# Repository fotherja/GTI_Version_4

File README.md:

# GTI_Version_4
This repo contains the hardware and software files for GTIv4. This is being superseded by GTIv5 (https://github.com/fotherja/Grid_Tie_Inverter_V5)

Hardware:
KiCad was used to design the 4-Layer PCB. This was manufactured by <a href="https://www.pcbway.com/">PCBWay</a> (They produce good quality PCBs for competitive prices with excellent turnaround times).

The board uses gallium nitride MASTERGAN2s and an isolated driver chip. Four AMC1306 isolated current shunt modulators read the various analogue signals and an STM32L475 powers the board.    

Problems: 1) The EMC filter capacitors are incorrectly connected up. It may reduce the performance of the EMI filtering. 2) On testing, at about 300 Watts one of the MASTERGAN2s exploded. The exact reason is unclear and so this hardware has been redesigned into V5.

Software:
Software was developed in STM32CubeIDE. We got as far as implementing a PR controller which was extremely working well. Needs lots more work though.

Problems: I did not manage to get the DFSDM analogue watchdog feature working to provide protection in case of overcurrent or overvoltage. I asked the question on StackOverflow but got no answers (https://stackoverflow.com/questions/75287992/cant-get-the-analogue-watchdog-to-trigger-an-interrupt-on-the-dfsdm-peripheral)

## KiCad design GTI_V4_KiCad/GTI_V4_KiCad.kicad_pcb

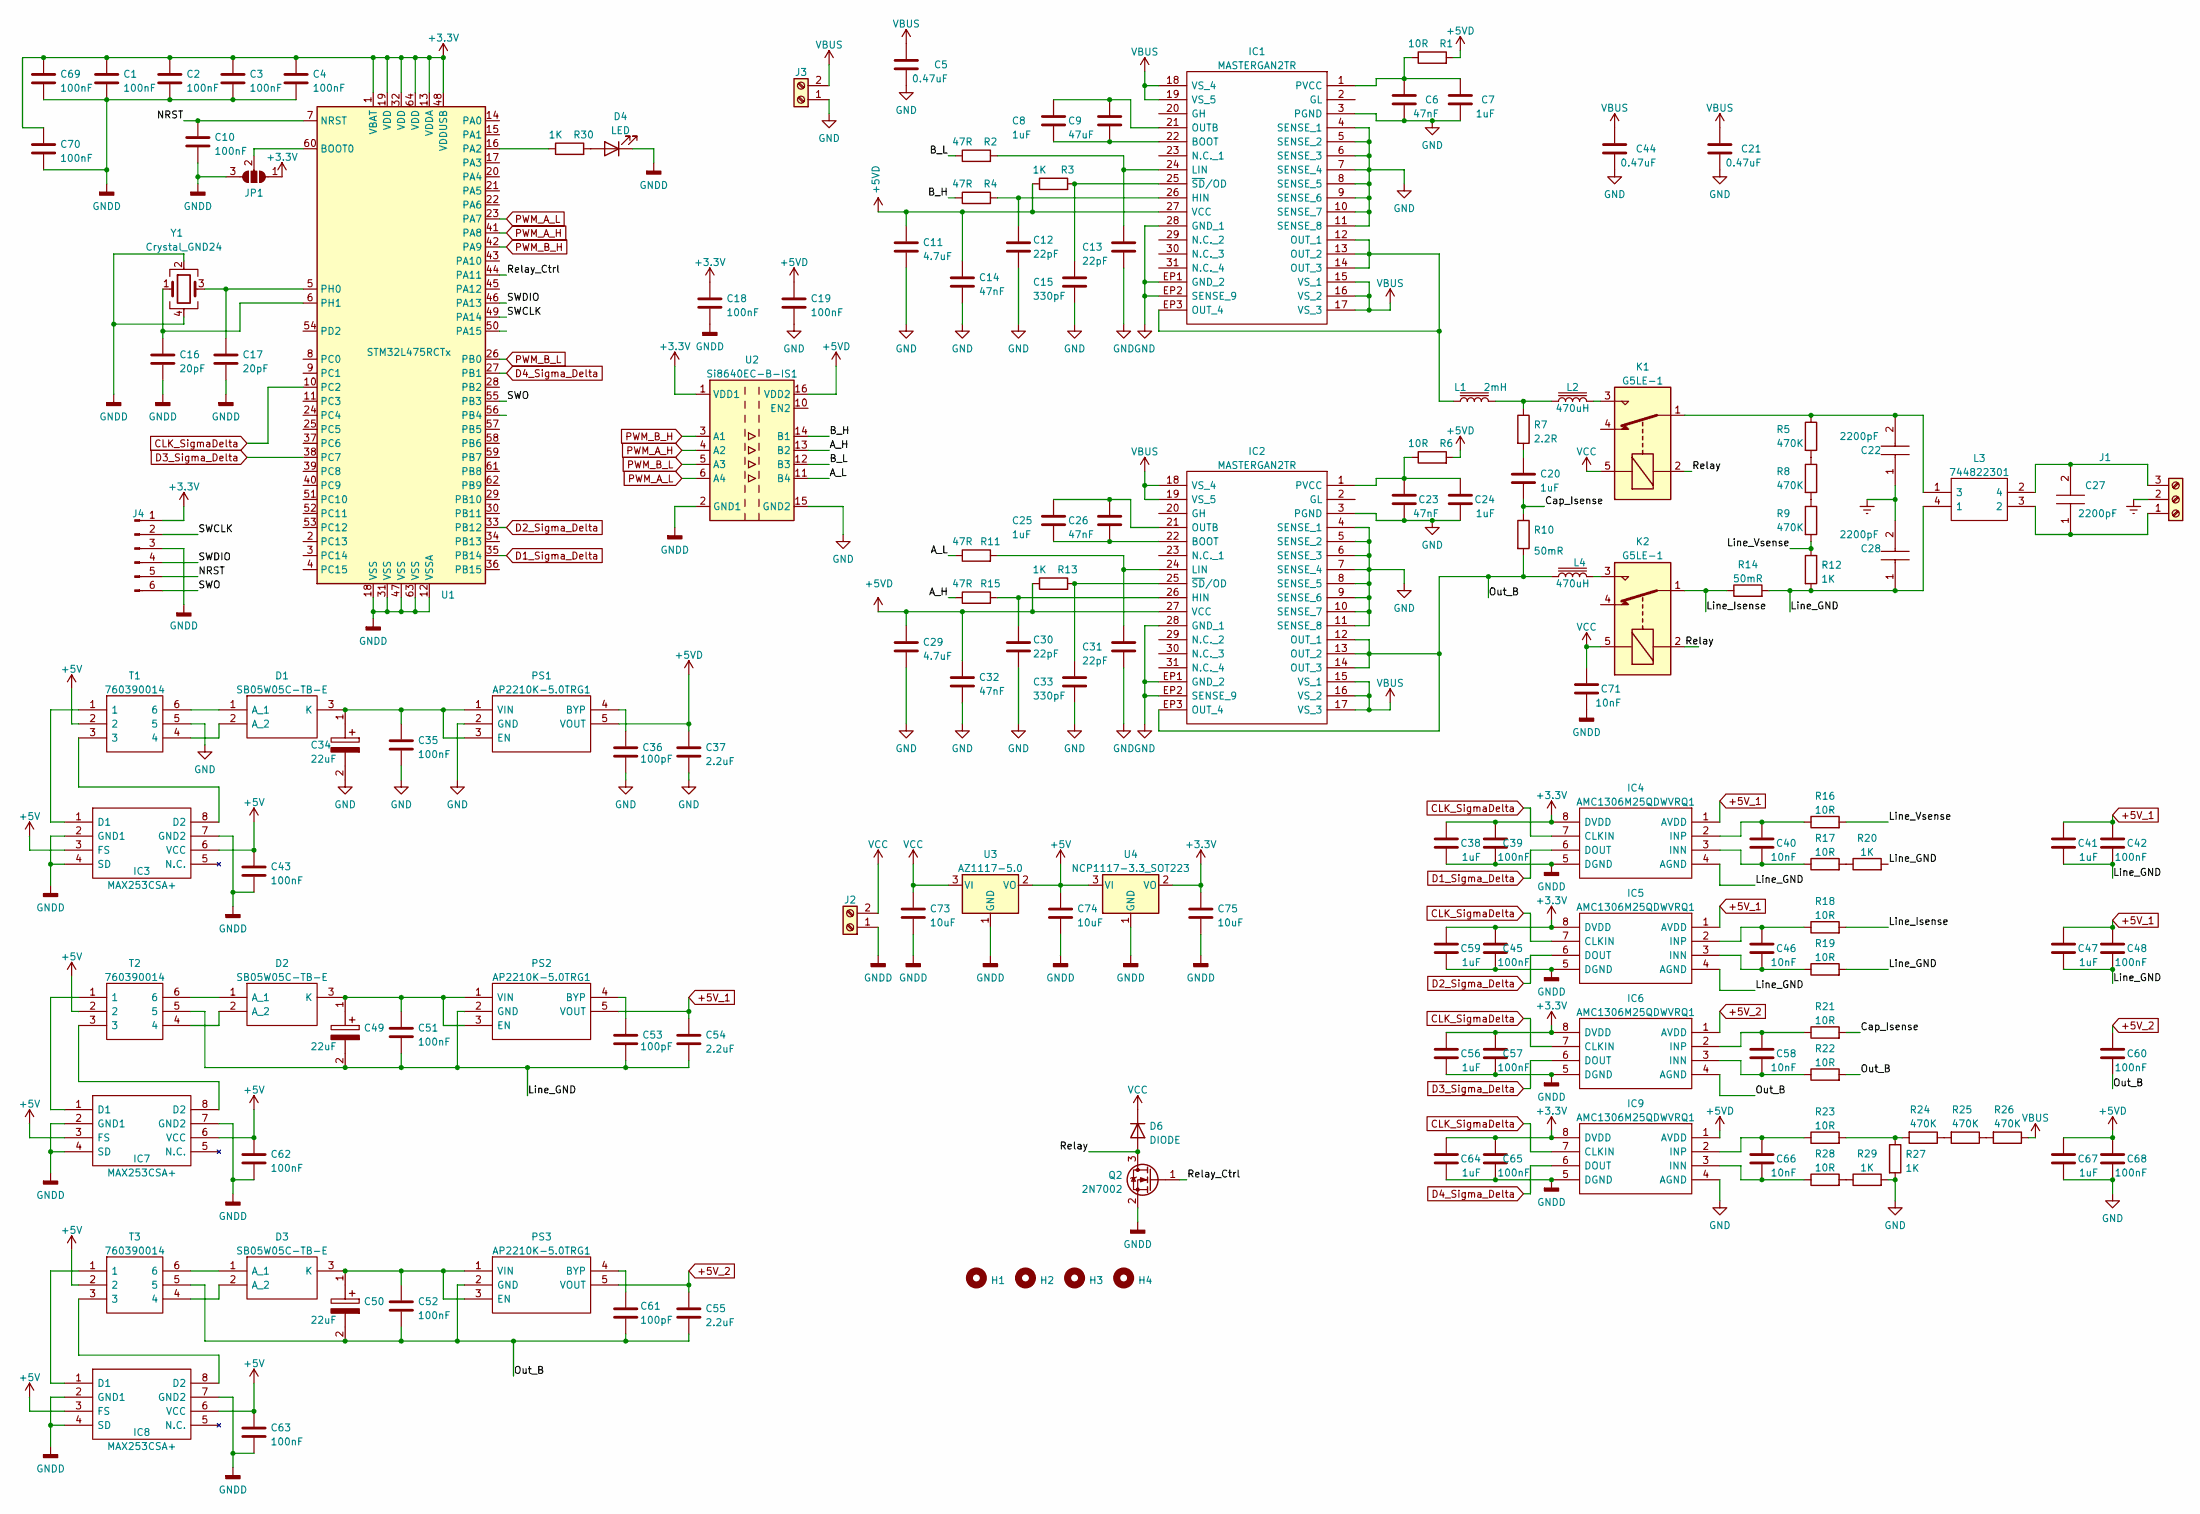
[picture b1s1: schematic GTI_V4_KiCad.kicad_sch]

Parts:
C1, C2, C3, C4, C10, C18, C19, C35, C39, C42, C43, C45, C48, C51, C52, C57, C60, C62, C63, C65, C68, C69, C70: 100nF; C_0603_1608Metric
C5, C21: 0.47uF; C_2225_5664Metric
C6, C14, C23, C26, C32: 47nF; C_0402_1005Metric
C7, C8, C24, C25, C38, C41, C47, C56, C59, C64, C67: 1uF; C_0603_1608Metric
C9: 47uF; C_0402_1005Metric
C11, C29: 4.7uF; C_0603_1608Metric
C12, C13, C30, C31: 22pF; C_0603_1608Metric
C15, C33: 330pF; C_0603_1608Metric
C16, C17: 20pF; C_0603_1608Metric
C20: 1uF; C_Rect_L27.0mm_W11.0mm_P22.00mm
C22, C27, C28: 2200pF; C901U222MZVDBA7317; Mouser Part Number 80-C901U222MZVDBAP
C34, C49, C50: 22uF; CAPPC3328X220N; Mouser Part Number 74-595D226X9020B2T
C36, C53, C61: 100pF; C_0603_1608Metric
C37, C54, C55: 2.2uF; C_0603_1608Metric
C40, C46, C58, C66, C71: 10nF; C_0603_1608Metric
C44: 0.47uF; C_Rect_L31.5mm_W17.0mm_P27.50mm_MKS4
C73: 10uF; C_0805_2012Metric
C74, C75: 10uF; C_0603_1608Metric
D1, D2, D3: SB05W05C-TB-E; SOT95P250X135-3N; Mouser Part Number 863-SB05W05C-TB-E
D4: LED; LED_0603_1608Metric
D6: DIODE; DIOM5227X250N
H1, H2, H3, H4: MountingHole; MountingHole_3.2mm_M3
IC1, IC2: MASTERGAN2TR; Mouser Part Number 511-MASTERGAN2TR
IC3, IC7, IC8: MAX253CSA+; SOIC127P600X175-8N; Mouser Part Number 700-MAX253CSA
IC4, IC5, IC6, IC9: AMC1306M25QDWVRQ1; SOIC127P1150X280-8N; Mouser Part Number 595-MC1306M25QDWVRQ1
J1: Screw_Terminal_01x03; TerminalBlock_bornier-3_P5.08mm
J2, J3: Screw_Terminal_01x02; TerminalBlock_bornier-2_P5.08mm
J4: Conn_01x06_Male; PinHeader_1x06_P1.27mm_Vertical
JP1: SolderJumper_3_Open; SolderJumper-3_P1.3mm_Open_RoundedPad1.0x1.5mm
K1, K2: G5LE-1; Relay_SPDT_Omron-G5LE-1
L1: 2mH; L_Toroid_Vertical_L35.1mm_W21.1mm_P18.50mm_Vishay_TJ6
L2, L4: 470uH; L_Toroid_Vertical_L41.9mm_W19.1mm_P15.80mm_Vishay_TJ7
L3: 744822301; WE-CMB_S5; Mouser Part Number 710-744822301
PS1, PS2, PS3: AP2210K-5.0TRG1; SOT95P282X130-5N; Mouser Part Number 621-AP2210K-5.0TRG1
Q2: 2N7002; SOT-23
R1, R6, R16, R17, R18, R19, R21, R22, R23, R28: 10R; R_0603_1608Metric
R2, R4, R11, R15: 47R; R_0603_1608Metric
R3, R12, R13, R20, R27, R29, R30: 1K; R_0603_1608Metric
R5, R8, R9, R24, R25, R26: 470K; R_0805_2012Metric
R7: 2.2R; R_2512_6332Metric
R10, R14: 50mR; R_2512_6332Metric
T1, T2, T3: 760390014; 760390015; Mouser Part Number 710-760390014
U1: STM32L475RCTx; LQFP-64_10x10mm_P0.5mm
U2: Si8640EC-B-IS1; SOIC-16_3.9x9.9mm_P1.27mm
U3: AZ1117-5.0; AZ1117CD50TRG1
U4: NCP1117-3.3_SOT223; SOT-223-3_TabPin2
Y1: Crystal_GND24; Crystal_SMD_Abracon_ABM10-4Pin_2.5x2.0mm

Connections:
+3.3V: C1.1, C2.1, C3.1, C4.1, C18.1, C38.1, C39.1, C45.1, C56.1, C57.1, C59.1, C64.1, C65.1, C69.1, C70.1, C75.1, IC4.8 (DVDD), IC5.8 (DVDD), IC6.8 (DVDD), IC9.8 (DVDD), J4.1, JP1.1 (A), U1.1 (VBAT), U1.13 (VDDA), U1.19 (VDD), U1.32 (VDD), U1.48 (VDDUSB), U1.64 (VDD), U2.1 (VDD1), U4.2 (VO)
+5V: C43.1, C62.1, C63.1, C74.1, IC3.3 (FS), IC3.6 (VCC), IC7.3 (FS), IC7.6 (VCC), IC8.3 (FS), IC8.6 (VCC), T1.2, T2.2, T3.2, U3.2 (VO), U4.3 (VI)
+5VD: C11.1, C14.1, C19.1, C29.1, C32.1, C37.1, C67.1, C68.1, IC1.27 (VCC), IC2.27 (VCC), IC9.1 (AVDD), PS1.5 (VOUT), R1.2, R3.1, R6.2, R13.1, U2.16 (VDD2)
+5V_1: C41.1, C42.1, C47.1, C48.1, C54.1, IC4.1 (AVDD), IC5.1 (AVDD), PS2.5 (VOUT)
+5V_2: C55.1, C60.1, IC6.1 (AVDD), PS3.5 (VOUT)
/A_H: R15.1, U2.13 (B2)
/A_L: R11.1, U2.11 (B4)
/B_H: R4.1, U2.14 (B1)
/B_L: R2.1, U2.12 (B3)
/Cap_Isense: C20.2, R10.1, R21.2
/Line_GND: C28.1, C41.2, C42.2, C47.2, C48.2, C49.2, C51.2, C53.2, C54.2, IC4.4 (AGND), IC5.4 (AGND), L3.4 (1), PS2.2 (GND), R12.2, R14.2, R19.2, R20.2, T2.5
/Line_Isense: K2.1, R14.1, R18.2
/Line_Vsense: R9.2, R12.1, R16.2
/NRST: C10.1, J4.5, U1.7 (NRST)
/Out_B: C50.2, C52.2, C55.2, C60.2, C61.2, IC2.12 (OUT_1), IC2.13 (OUT_2), IC2.14 (OUT_3), IC2.EP3 (OUT_4), IC6.4 (AGND), L4.1, PS3.2 (GND), R10.2, R22.2, T3.5
/Relay: D6.1 (A), K1.2, K2.2, Q2.3 (D)
/Relay_Ctrl: Q2.1 (G), U1.44 (PA11)
/SWCLK: J4.2, U1.49 (PA14)
/SWDIO: J4.4, U1.46 (PA13)
/SWO: J4.6, U1.55 (PB3)
CLK_SigmaDelta: IC4.7 (CLKIN), IC5.7 (CLKIN), IC6.7 (CLKIN), IC9.7 (CLKIN), U1.10 (PC2)
D1_Sigma_Delta: IC4.6 (DOUT), U1.35 (PB14)
D2_Sigma_Delta: IC5.6 (DOUT), U1.33 (PB12)
D3_Sigma_Delta: IC6.6 (DOUT), U1.38 (PC7)
D4_Sigma_Delta: IC9.6 (DOUT), U1.27 (PB1)
Earth: C22.1, C28.2, J1.2
GND: C5.2, C6.2, C7.2, C11.2, C12.2, C13.2, C14.2, C15.2, C19.2, C21.2, C23.2, C24.2, C29.2, C30.2, C31.2, C32.2, C33.2, C34.2, C35.2, C36.2, C37.2, C44.2, C67.2, C68.2, IC1.3 (PGND), IC1.4 (SENSE_1), IC1.5 (SENSE_2), IC1.6 (SENSE_3), IC1.7 (SENSE_4), IC1.8 (SENSE_5), IC1.9 (SENSE_6), IC1.10 (SENSE_7), IC1.11 (SENSE_8), IC1.28 (GND_1), IC1.EP1 (GND_2), IC1.EP2 (SENSE_9), IC2.3 (PGND), IC2.4 (SENSE_1), IC2.5 (SENSE_2), IC2.6 (SENSE_3), IC2.7 (SENSE_4), IC2.8 (SENSE_5), IC2.9 (SENSE_6), IC2.10 (SENSE_7), IC2.11 (SENSE_8), IC2.28 (GND_1), IC2.EP1 (GND_2), IC2.EP2 (SENSE_9), IC9.4 (AGND), J3.1, PS1.2 (GND), R27.2, R29.2, T1.5, U2.9 (GND2), U2.15 (GND2)
GNDD: C1.2, C2.2, C3.2, C4.2, C10.2, C16.2, C17.2, C18.2, C38.2, C39.2, C43.2, C45.2, C56.2, C57.2, C59.2, C62.2, C63.2, C64.2, C65.2, C69.2, C70.2, C71.2, C73.2, C74.2, C75.2, D4.1 (K), IC3.2 (GND1), IC3.4 (SD), IC3.7 (GND2), IC4.5 (DGND), IC5.5 (DGND), IC6.5 (DGND), IC7.2 (GND1), IC7.4 (SD), IC7.7 (GND2), IC8.2 (GND1), IC8.4 (SD), IC8.7 (GND2), IC9.5 (DGND), J2.1, J4.3, JP1.3 (B), Q2.2 (S), U1.12 (VSSA), U1.18 (VSS), U1.31 (VSS), U1.47 (VSS), U1.63 (VSS), U2.2 (GND1), U2.8 (GND1), U3.1 (GND), U4.1 (GND), Y1.2, Y1.4
unnamed: C6.1, C7.1, IC1.1 (PVCC), R1.1
unnamed: C8.1, C9.1, IC1.21 (OUTB)
unnamed: C8.2, C9.2, IC1.22 (BOOT)
unnamed: C12.1, IC1.26 (HIN), R4.2
unnamed: C13.1, IC1.24 (LIN), R2.2
unnamed: C15.1, IC1.25 (~SD/OD), R3.2
unnamed: C16.1, U1.6 (PH1), Y1.1
unnamed: C17.1, U1.5 (PH0), Y1.3
unnamed: C20.1, R7.2
unnamed: C22.2, K1.1, L3.1 (3), R5.1
unnamed: C23.1, C24.1, IC2.1 (PVCC), R6.1
unnamed: C25.1, C26.1, IC2.21 (OUTB)
unnamed: C25.2, C26.2, IC2.22 (BOOT)
unnamed: C27.1, J1.1, L3.3 (2)
unnamed: C27.2, J1.3, L3.2 (4)
unnamed: C30.1, IC2.26 (HIN), R15.2
unnamed: C31.1, IC2.24 (LIN), R11.2
unnamed: C33.1, IC2.25 (~SD/OD), R13.2
unnamed: C34.1, C35.1, D1.3 (K), PS1.1 (VIN), PS1.3 (EN)
unnamed: C36.1, PS1.4 (BYP)
unnamed: C40.1, IC4.2 (INP), R16.1
unnamed: C40.2, IC4.3 (INN), R17.1
unnamed: C46.1, IC5.2 (INP), R18.1
unnamed: C46.2, IC5.3 (INN), R19.1
unnamed: C49.1, C51.1, D2.3 (K), PS2.1 (VIN), PS2.3 (EN)
unnamed: C50.1, C52.1, D3.3 (K), PS3.1 (VIN), PS3.3 (EN)
unnamed: C53.1, PS2.4 (BYP)
unnamed: C58.1, IC6.2 (INP), R21.1
unnamed: C58.2, IC6.3 (INN), R22.1
unnamed: C61.1, PS3.4 (BYP)
unnamed: C66.1, IC9.2 (INP), R23.1
unnamed: C66.2, IC9.3 (INN), R28.1
unnamed: D1.1 (A_1), T1.6
unnamed: D1.2 (A_2), T1.4
unnamed: D2.1 (A_1), T2.6
unnamed: D2.2 (A_2), T2.4
unnamed: D3.1 (A_1), T3.6
unnamed: D3.2 (A_2), T3.4
unnamed: D4.2 (A), R30.2
unnamed: IC1.12 (OUT_1), IC1.13 (OUT_2), IC1.14 (OUT_3), IC1.EP3 (OUT_4), L1.1
unnamed: IC3.1 (D1), T1.1
unnamed: IC3.8 (D2), T1.3
unnamed: IC7.1 (D1), T2.1
unnamed: IC7.8 (D2), T2.3
unnamed: IC8.1 (D1), T3.1
unnamed: IC8.8 (D2), T3.3
unnamed: JP1.2 (C), U1.60 (BOOT0)
unnamed: K1.3, L2.2
unnamed: K2.3, L4.2
unnamed: L1.2, L2.1, R7.1
unnamed: R5.2, R8.1
unnamed: R8.2, R9.1
unnamed: R17.2, R20.1
unnamed: R23.2, R24.2, R27.1
unnamed: R24.1, R25.2
unnamed: R25.1, R26.2
unnamed: R28.2, R29.1
unnamed: R30.1, U1.16 (PA2)
PWM_A_H: U1.41 (PA8), U2.4 (A2)
PWM_A_L: U1.23 (PA7), U2.6 (A4)
PWM_B_H: U1.42 (PA9), U2.3 (A1)
PWM_B_L: U1.26 (PB0), U2.5 (A3)
VBUS: C5.1, C21.1, C44.1, IC1.15 (VS_1), IC1.16 (VS_2), IC1.17 (VS_3), IC1.18 (VS_4), IC1.19 (VS_5), IC2.15 (VS_1), IC2.16 (VS_2), IC2.17 (VS_3), IC2.18 (VS_4), IC2.19 (VS_5), J3.2, R26.1
VCC: C71.1, C73.1, D6.2 (K), J2.2, K1.5, K2.5, U3.3 (VI)

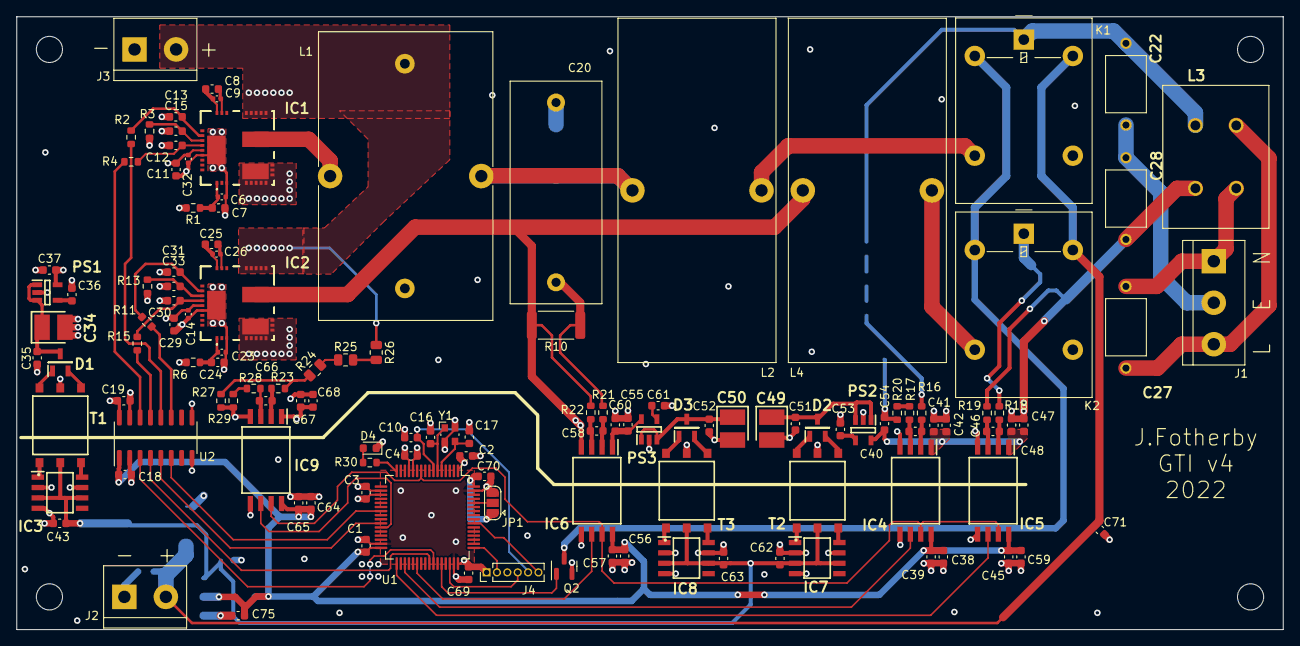
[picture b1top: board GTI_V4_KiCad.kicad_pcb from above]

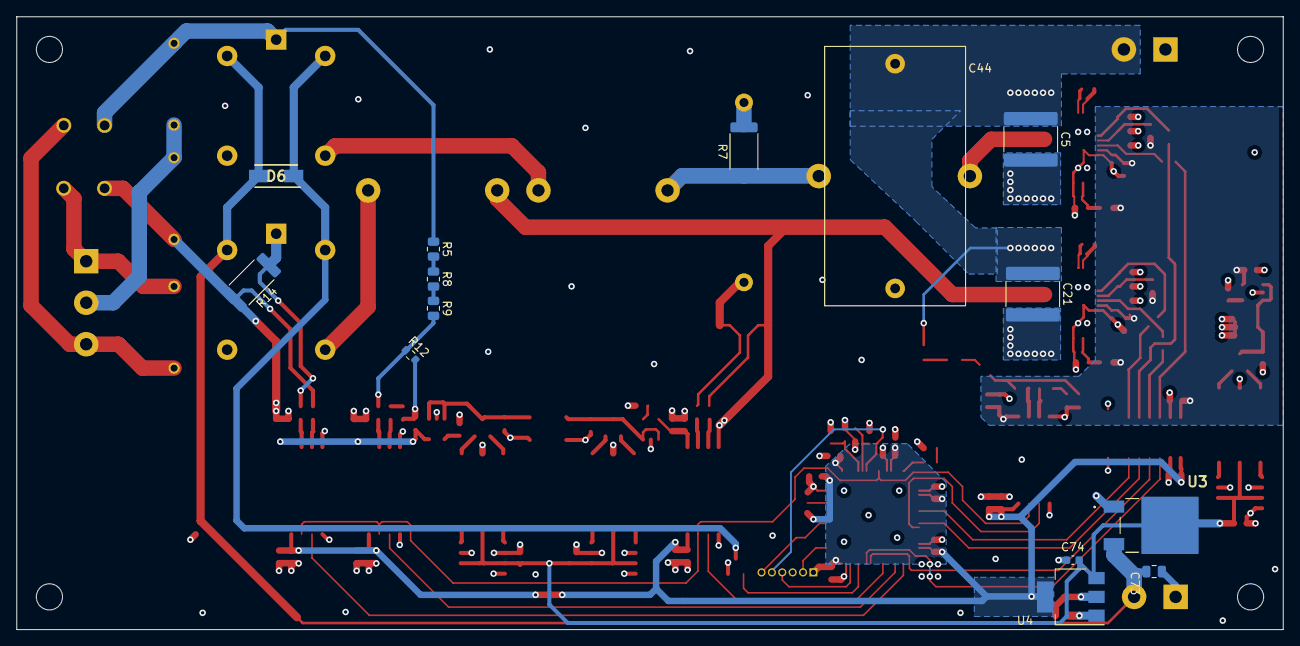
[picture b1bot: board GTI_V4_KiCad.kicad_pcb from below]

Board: 4 copper layers, 155.0 x 75.0 mm, 145 parts (14 on the bottom side), 92 nets.

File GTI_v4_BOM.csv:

Ref,Qnty,Value,Footprint,Link to Part
"C1, C2, C3, C4, C10, C18, C19, C35, C39, C42, C43, C45, C48, C51, C52, C57, C60, C62, C63, C65, C68, C69, C70, ",23,100nF,Capacitor_SMD:C_0603_1608Metric,
"C5, C21, ",2,0.47uF,Capacitor_SMD:C_2225_5664Metric,
"C6, C14, C23, C26, C32, ",5,47nF,Capacitor_SMD:C_0402_1005Metric,
"C7, C8, C24, C38, C41, C47, C56, C59, C64, C67, C71, ",11,1uF,Capacitor_SMD:C_0603_1608Metric,
"C9, ",1,47uF,Capacitor_SMD:C_0402_1005Metric,
"C11, C25, C29, ",3,4.7uF,Capacitor_SMD:C_0603_1608Metric,
"C12, C13, C30, C31, ",4,22pF,Capacitor_SMD:C_0603_1608Metric,
"C15, C33, ",2,330pF,Capacitor_SMD:C_0603_1608Metric,
"C16, C17, ",2,20pF,Capacitor_SMD:C_0603_1608Metric,
"C20, ",1,1uF,Capacitor_THT:C_Rect_L27.0mm_W11.0mm_P22.00mm,https://www.digikey.co.uk/en/products/detail/epcos-tdk-elect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
"C22, C27, C28, ",3,2200pF,C901U222MZVDBA7317:C901U222MZVDBA7317,https://www.mouser.co.uk/ProductDetail/KEMET/C901U222MZVDBA7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
"C34, C49, C50, ",3,22uF,595D226X9020:CAPPC3328X220N,https://www.mouser.co.uk/ProductDetail/Vishay-Sprague/595D22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
"C36, C53, C61, ",3,100pF,Capacitor_SMD:C_0603_1608Metric,
"C37, C54, C55, ",3,2.2uF,Capacitor_SMD:C_0603_1608Metric,
"C40, C46, C58, C66, ",4,10nF,Capacitor_SMD:C_0603_1608Metric,
"C44, ",1,0.47uF,Capacitor_THT:C_Rect_L31.5mm_W17.0mm_P27.50mm_MKS4,
"C73, ",1,10uF,Capacitor_SMD:C_0805_2012Metric,
"C74, C75, ",2,10uF,Capacitor_SMD:C_0603_1608Metric,
"D1, D2, D3, ",3,SB05W05C-TB-E,SB05W05C:SOT95P250X135-3N,https://www.mouser.co.uk/ProductDetail/onsemi/SB05W05C-TB-E?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
"D4, ",1,LED,LED_SMD:LED_0603_1608Metric,
"D6, ",1,DIODE,ES1J:DIOM5227X250N,
"H1, H2, H3, H4, ",4,MountingHole,MountingHole:MountingHole_3.2mm_M3,
"IC1, IC2, ",2,MASTERGAN2TR,MASTERGAN2:MASTERGAN2TR,https://www.mouser.co.uk/ProductDetail/STMicroelectronics/MA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
"IC3, IC7, IC8, ",3,MAX253CSA+,MAX253CSA:SOIC127P600X175-8N,https://www.mouser.co.uk/ProductDetail/Maxim-Integrated/MAX2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
"IC4, IC5, IC6, IC9, ",4,AMC1306M25QDWVRQ1,AMC1306:SOIC127P1150X280-8N,https://www.mouser.co.uk/ProductDetail/Texas-Instruments/AMC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
"J1, ",1,Screw_Terminal_01x03,TerminalBlock:TerminalBlock_bornier-3_P5.08mm,
"J2, J3, ",2,Screw_Terminal_01x02,TerminalBlock:TerminalBlock_bornier-2_P5.08mm,
"J4, ",1,Conn_01x06_Male,Connector_PinHeader_1.27mm:PinHeader_1x06_P1.27mm_Vertical,
"JP1, ",1,SolderJumper_3_Open,Jumper:SolderJumper-3_P1.3mm_Open_RoundedPad1.0x1.5mm,
"K1, K2, ",2,G5LE-1,Relay_THT:Relay_SPDT_Omron-G5LE-1,https://www.mouser.co.uk/ProductDetail/Omron-Electronics/G5L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
"L1, ",1,2mH,Inductor_THT:L_Toroid_Vertical_L35.1mm_W21.1mm_P18.50mm_Vishay_TJ6,
"L2, L4, ",2,470uH,Inductor_THT:L_Toroid_Vertical_L41.9mm_W19.1mm_P15.80mm_Vishay_TJ7,
"L3, ",1,744822301,744822301:WE-CMB_S5,https://www.mouser.co.uk/ProductDetail/Wurth-Elektronik/7448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
"PS1, PS2, PS3, ",3,AP2210K-5.0TRG1,AP2210K-5.0TRG1:SOT95P282X130-5N,https://www.mouser.co.uk/ProductDetail/Diodes-Incorporated/A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
"Q2, ",1,2N7002,Package_TO_SOT_SMD:SOT-23,
"R1, R6, R16, R17, R18, R19, R21, R22, R23, R28, ",10,10R,Resistor_SMD:R_0603_1608Metric,
"R2, R4, R11, R15, ",4,47R,Resistor_SMD:R_0603_1608Metric,
"R3, R12, R13, R20, R27, R29, R30, ",7,1K,Resistor_SMD:R_0603_1608Metric,
"R5, R8, R9, R24, R25, R26, ",6,470K,Resistor_SMD:R_0805_2012Metric,
"R7, ",1,6.8R,Resistor_SMD:R_2512_6332Metric,https://www.digikey.co.uk/en/products/detail/yageo/AC2512FK-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
"R10, R14, ",2,50mR,Resistor_SMD:R_2512_6332Metric,
"T1, T2, T3, ",3,760390014,760390014:760390015,https://www.mouser.co.uk/ProductDetail/Wurth-Elektronik/7603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
"U1, ",1,STM32L475RCTx,Package_QFP:LQFP-64_10x10mm_P0.5mm,https://www.mouser.co.uk/ProductDetail/STMicroelectronics/ST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
"U2, ",1,Si8640EC-B-IS1,Package_SO:SOIC-16_3.9x9.9mm_P1.27mm,https://www.digikey.co.uk/en/products/detail/skyworks-soluti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
"U3, ",1,AZ1117-5.0,AZ1117CD-5.0TRG1:AZ1117CD50TRG1,https://www.mouser.co.uk/ProductDetail/Diodes-Incorporated/A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
"U4, ",1,NCP1117-3.3_SOT223,Package_TO_SOT_SMD:SOT-223-3_TabPin2,
"Y1, ",1,Crystal_GND24,Crystal:Crystal_SMD_Abracon_ABM10-4Pin_2.5x2.0mm,

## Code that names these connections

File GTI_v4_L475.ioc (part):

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Mcu.Name=STM32L475R(C-E-G)Tx
Mcu.Package=LQFP64
Mcu.UserName=STM32L475RCTx
PA11.GPIOParameters=GPIO_Speed,GPIO_Label
PA11.GPIO_Label=Relay
PA11.GPIO_Speed=GPIO_SPEED_FREQ_MEDIUM
PA11.Signal=GPIO_Output
PA2.GPIOParameters=GPIO_Speed,PinState,GPIO_Label
PA2.GPIO_Label=LED
PA2.GPIO_Speed=GPIO_SPEED_FREQ_MEDIUM
PA2.PinState=GPIO_PIN_RESET
PA2.Signal=GPIO_Output
PA7.GPIOParameters=GPIO_Speed,GPIO_Label
PA7.GPIO_Label=Phase_BN
PA7.GPIO_Speed=GPIO_SPEED_FREQ_VERY_HIGH
PA7.Mode=PWM Generation1 CH1 CH1N
PA7.Signal=TIM1_CH1N
PA8.GPIOParameters=GPIO_Speed,GPIO_Label
PA8.GPIO_Label=Phase_B
PA8.GPIO_Speed=GPIO_SPEED_FREQ_VERY_HIGH
PA8.Signal=S_TIM1_CH1
PA9.GPIOParameters=GPIO_Speed,GPIO_Label
PA9.GPIO_Label=Phase_A
PA9.GPIO_Speed=GPIO_SPEED_FREQ_VERY_HIGH
PA9.Signal=S_TIM1_CH2
PB0.GPIOParameters=GPIO_Speed,GPIO_Label
PB0.GPIO_Label=Phase_AN
PB0.GPIO_Speed=GPIO_SPEED_FREQ_VERY_HIGH
PB0.Mode=PWM Generation2 CH2 CH2N
PB0.Signal=TIM1_CH2N
PB1.GPIOParameters=GPIO_Speed,GPIO_Label
PB1.GPIO_Label=Vbus_DIN
PB1.GPIO_Speed=GPIO_SPEED_FREQ_VERY_HIGH
PB1.Signal=S_DATAIN0DFSDM1
PB12.GPIOParameters=GPIO_Speed,GPIO_Label
PB12.GPIO_Label=Igrid_DIN
PB12.GPIO_Speed=GPIO_SPEED_FREQ_VERY_HIGH
PB12.Signal=S_DATAIN1DFSDM1
PB14.GPIOParameters=GPIO_Speed,GPIO_Label
PB14.GPIO_Label=Vgrid_DIN
PB14.GPIO_Speed=GPIO_SPEED_FREQ_VERY_HIGH
PB14.Signal=S_DATAIN2DFSDM1
PC2.GPIOParameters=GPIO_Speed,GPIO_Label
PC2.GPIO_Label=DFSDM_Clk
PC2.GPIO_Speed=GPIO_SPEED_FREQ_VERY_HIGH
PC2.Signal=S_CKOUTDFSDM1
PC7.GPIOParameters=GPIO_Speed,GPIO_Label
PC7.GPIO_Label=Icap_DIN
PC7.GPIO_Speed=GPIO_SPEED_FREQ_VERY_HIGH
PC7.Signal=S_DATAIN3DFSDM1
PH0-OSC_IN\ (PH0).Mode=HSE-External-Oscillator
PH0-OSC_IN\ (PH0).Signal=RCC_OSC_IN
PH1-OSC_OUT\ (PH1).Mode=HSE-External-Oscillator
PH1-OSC_OUT\ (PH1).Signal=RCC_OSC_OUT
RCC.HSE_VALUE=16000000
RCC.SYSCLKFreq_VALUE=80000000
RCC.SYSCLKSource=RCC_SYSCLKSOURCE_PLLCLK
board=custom

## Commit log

2022-12-27 Not yet finished PCB
    Nearly finished. Just checking, double checking and triple checking all pins, chips and connections.
2023-01-01 99% finished PCB
2023-01-01 Completed PCB - sent for fabrication
    Sent to PCBWay for fabrication
2023-02-16 Uploaded BOM
2023-02-16 The finished and used PCB
2023-02-16 Finished and used Schematic and PCB
2023-02-16 Good papers and articles
2023-02-22 adding the writeup
2023-03-15 update BOM - to add XO part number and link
